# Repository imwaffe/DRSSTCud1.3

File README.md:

# DRSSTCud1.3
Universal Driver for DRSSTC (Dual-Resonant Solid-State Tesla Coil) based on Steve Ward's universal driver design.<br>
For the driving section, a pair of UCC3732x drivers drive two totem poles of N and P channel mosfets, allowing for higher current capabilities required for large bricks IGBTs.

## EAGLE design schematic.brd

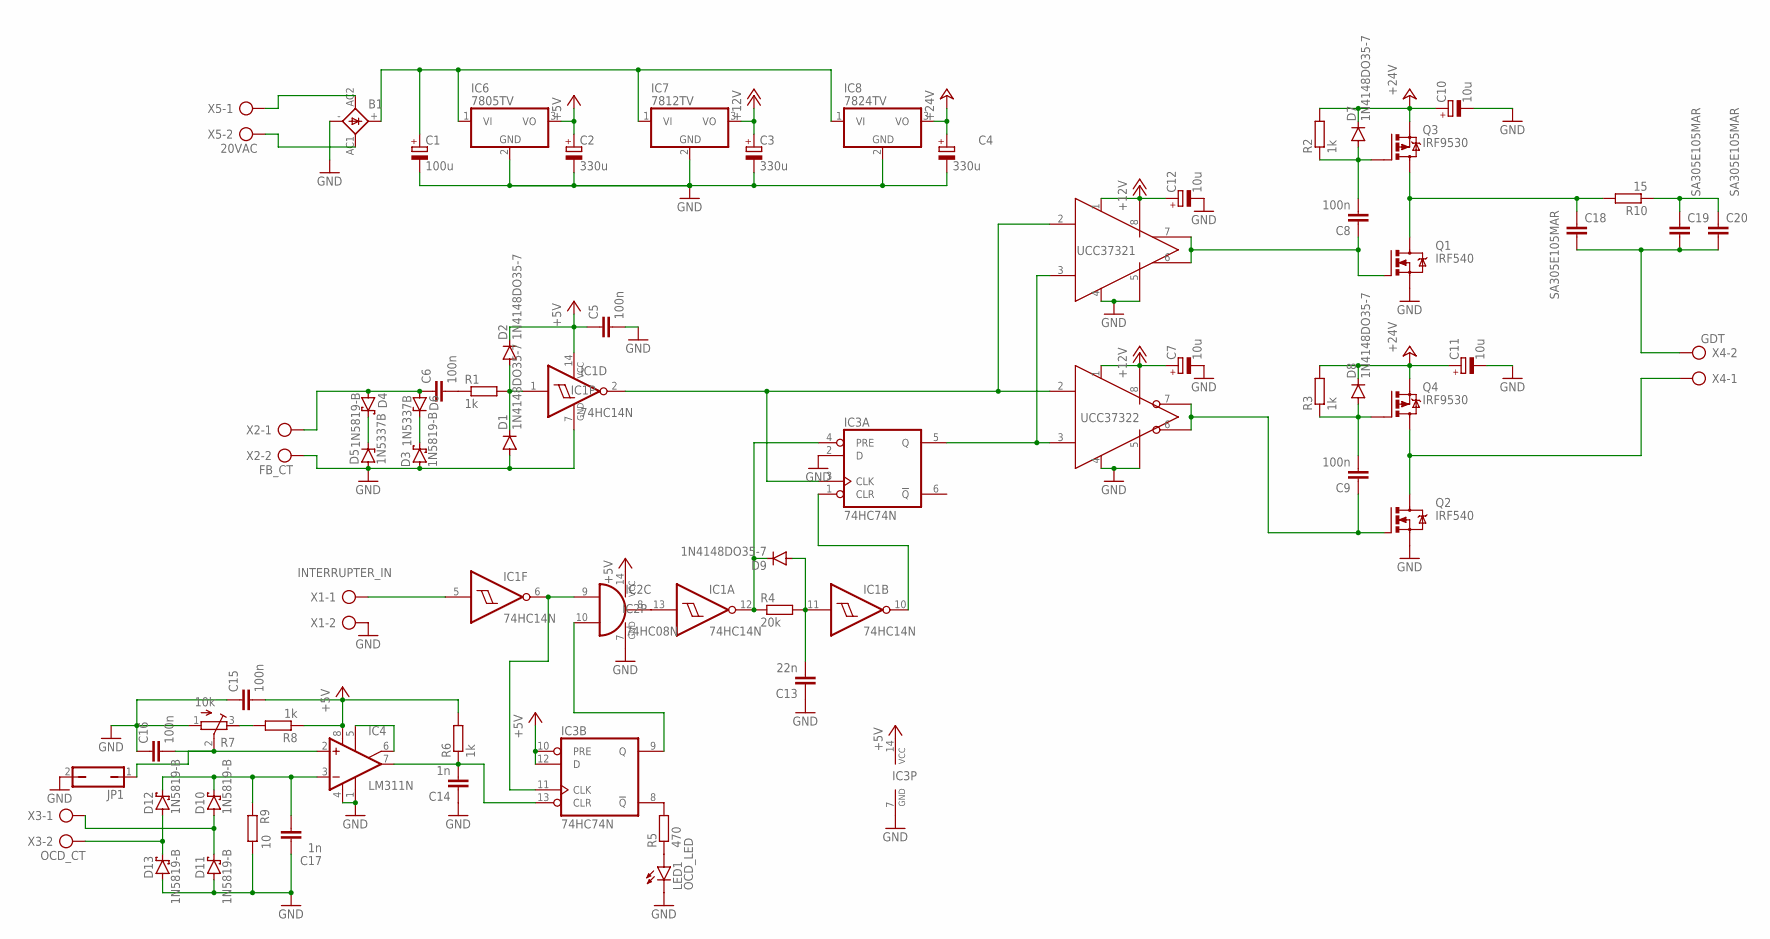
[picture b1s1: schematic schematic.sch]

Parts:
B1: KBL
C1: 100u; E3,5-10
C2, C3, C4: 330u; E3,5-10
C5, C6, C8, C9, C15, C16: 100n; C050-030X075
C7, C10, C11, C12: 10u; E2,5-6
C13: 22n; C050-030X075
C14, C17: 1n; C050-030X075
C18, C19, C20: SA305E105MAR; C050-025X075
D1, D2, D7, D8, D9: 1N4148DO35-7; DO35-7
D3, D4, D10, D11, D12, D13: 1N5819-B; DO41-7.6
D5, D6: 1N5337B; DO41Z10
IC1: 74HC14N; DIL14
IC2: 74HC08N; DIL14
IC3: 74HC74N; DIL14
IC4: LM311N; DIL08
IC5: UCC37321DIL8; DIL08
IC6: 7805TV; TO220V
IC7: 7812TV; TO220V
IC8: 7824TV; TO220V
IC9: UCC37322DIL8; DIL08
JP1: JP1Q; JP1
LED1: OCD_LED; LED3MM
Q1, Q2: IRF540; TO220BV
Q3, Q4: IRF9530; TO220BV
R1, R2, R3, R6, R8: 1k; 0204/7
R4: 20k; 0204/7
R5: 470; 0204/7
R7: 10k; RTRIM64X
R9: 10; 0411/15
R10: 15; 0204/7
X1: INTERRUPTER_IN; AK300/2
X2: FB_CT; AK300/2
X3: OCD_CT; AK300/2
X4: GDT; AK300/2
X5: 20VAC; AK300/2

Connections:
+5V: C2.+, C5.1, C15.2, D2.C, IC1.14 (VCC), IC2.14 (VCC), IC3.10 (PRE), IC3.12 (D), IC3.14 (VCC), IC4.8 (V+), IC6.3 (VO), R6.2, R8.1
+12V: C3.+, C7.+, C12.+, IC5.1 (1_VDD), IC5.8 (8_VDD), IC7.3 (VO), IC9.1 (1_VDD), IC9.8 (8_VDD)
+24V: C4.+, C10.+, C11.+, D7.C, D8.C, IC8.3 (VO), Q3.S, Q4.S, R2.2, R3.2
GND: B1.-, C1.-, C2.-, C3.-, C4.-, C5.2, C7.-, C10.-, C11.-, C12.-, C13.1, C14.1, C15.1, C16.1, C17.1, D1.A, D3.A, D5.A, D11.A, D13.A, IC1.7 (GND), IC2.7 (GND), IC3.2 (D), IC3.7 (GND), IC4.1 (GND), IC4.4 (V-), IC5.4 (4_AGND), IC5.5 (5_PGND), IC6.2 (GND), IC7.2 (GND), IC8.2 (GND), IC9.4 (4_AGND), IC9.5 (5_PGND), JP1.2, LED1.K (C), Q1.S, Q2.S, R7.1 (A), R9.2, X1.2, X2.2
unnamed: B1.+, C1.+, IC6.1 (VI), IC7.1 (VI), IC8.1 (VI)
unnamed: B1.AC2 (AC1), X5.1
unnamed: B1.AC1 (AC2), X5.2
unnamed: D1.C, D2.A, IC1.1 (I), R1.2
unnamed: C6.2, R1.1
unnamed: C6.1, D4.A, D6.A, X2.1
unnamed: D3.C, D6.C
unnamed: D4.C, D5.C
unnamed: IC1.2 (O), IC3.3 (CLK), IC5.2 (2_IN), IC9.2 (2_IN)
unnamed: C8.1, IC5.6 (6_OUT), IC5.7 (7_OUT), Q1.G
unnamed: IC3.5 (Q), IC5.3 (3_ENBL), IC9.3 (3_ENBL)
unnamed: C9.1, IC9.6 (6_OUT), IC9.7 (7_OUT), Q2.G
unnamed: IC1.10 (O), IC3.1 (CLR)
unnamed: C9.2, D8.A, Q4.G, R3.1
unnamed: D9.C, IC1.12 (O), IC3.4 (PRE), R4.1
unnamed: C13.2, D9.A, IC1.11 (I), R4.2
unnamed: C8.2, D7.A, Q3.G, R2.1
unnamed: Q2.D, Q4.D, X4.1
unnamed: C18.1, Q1.D, Q3.D, R10.2
unnamed: IC1.13 (I), IC2.8 (O)
unnamed: C19.1, C20.1, R10.1
unnamed: IC2.10 (I1), IC3.9 (Q)
unnamed: IC3.8 (!Q), R5.2
unnamed: LED1.A, R5.1
unnamed: IC1.6 (O), IC2.9 (I0), IC3.11 (CLK)
unnamed: IC4.5 (ON), IC4.6 (ON/STR)
unnamed: C16.2, IC4.2 (+IN), JP1.1, R7.2 (S)
unnamed: R7.3 (E), R8.2
unnamed: C17.2, D10.C, D12.C, IC4.3 (-IN), R9.1
unnamed: C14.2, IC3.13 (CLR), IC4.7 (OUT), R6.1
unnamed: D10.A, D11.C, X3.1
unnamed: D12.A, D13.C, X3.2
unnamed: C18.2, C19.2, C20.2, X4.2
unnamed: IC1.5 (I), X1.1

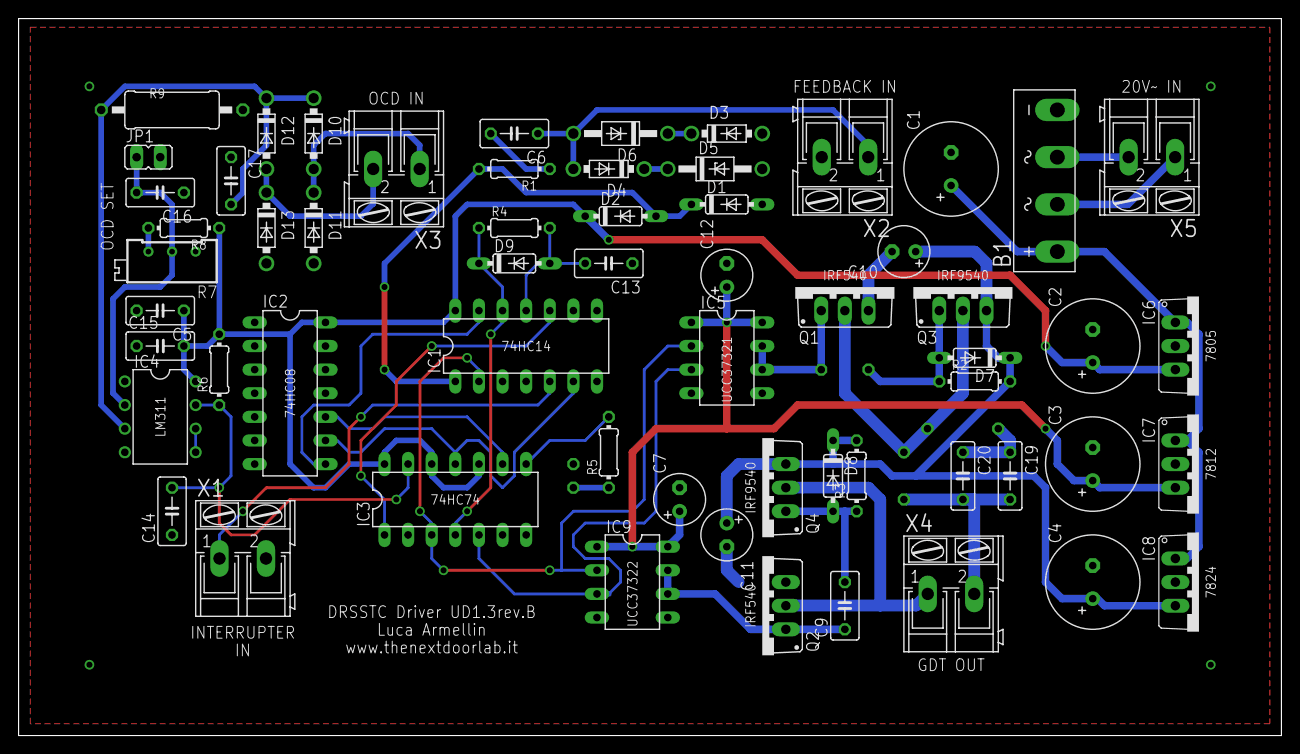
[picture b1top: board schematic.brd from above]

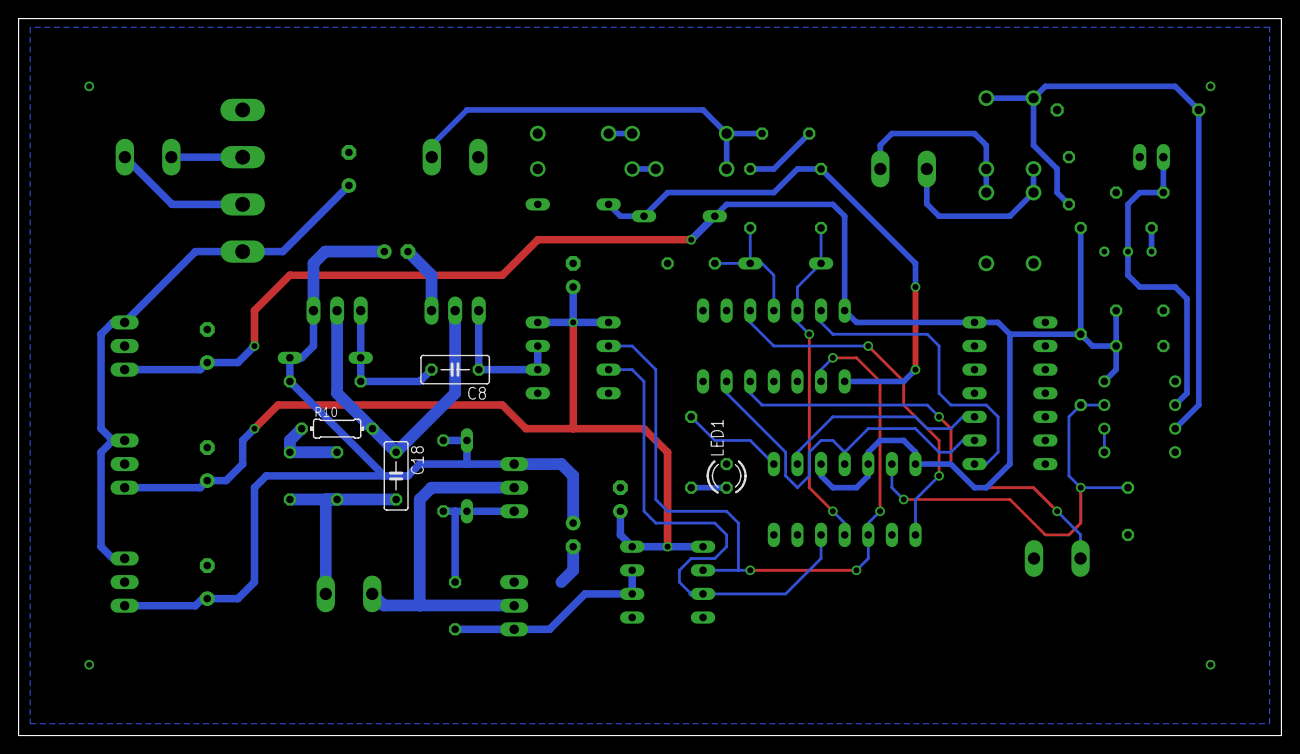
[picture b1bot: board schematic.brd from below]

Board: 2 copper layers, 135.9 x 77.1 mm, 64 parts (4 on the bottom side), 38 nets.

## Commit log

2020-03-23 Start
